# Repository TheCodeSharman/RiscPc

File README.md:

# RiscPc Repair Resources

This repository contains a collection of resources usefull for Risc PC repair.

The Risc OS 3.6.0 ROM source code is available at `external/Kernel`.

In order to view the POST messages refer to `ACORN_POST.md` that documents using a logic analsyer with a couple of resisters and a diode. This avoids needing to obtain/build a POST unit.

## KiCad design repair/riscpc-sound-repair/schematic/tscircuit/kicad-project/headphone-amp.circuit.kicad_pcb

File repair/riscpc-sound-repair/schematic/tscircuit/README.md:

# tscircuit evaluation

The same headphone amplifier as [`../headphone_amp.py`](../headphone_amp.py),
written in [tscircuit](https://tscircuit.com) instead of schemdraw — to answer
one question: **can you describe a circuit declaratively and have software
apply schematic conventions for you?**

Short answer: **yes, and it works.** Every component here is placed and every
net routed by tscircuit, from a file that contains no coordinates at all. But
the conventions it applies are weaker than a human's, and the result is
noticeably less readable than the hand-conventioned schemdraw drawing.

## Running

```bash
nix develop .#tscircuit --command make -C repair/riscpc-sound-repair/schematic/tscircuit
nix develop .#tscircuit --command make -C repair/riscpc-sound-repair/schematic/tscircuit kicad
```

`node`, `bun` (the CLI shells out to it) and `rsvg-convert` come from the
`tscircuit` devShell in `flake.nix` — kept separate from `default` so the
everyday shell stays lean. Deps come from npm, not nixpkgs.

Committed: `headphone-amp.svg`, `netlist.txt`, `package-lock.json`, and
`kicad-project/` — the extracted KiCad project.
Gitignored: `node_modules/`, the `.zip`, KiCad's `~*.lck` locks, and
`kicad-project/3dmodels/` (2.6 MB of STEP, regenerable).

**`kicad-project/` is tracked on purpose.** It starts out derived, but the
whole point of exporting to KiCad is to hand-tidy the layout there — and the
moment it is edited it stops being derived and becomes source. So it is
committed as text (`.kicad_sch`, `.kicad_pcb` and `.kicad_pro` are all
s-expressions or JSON, and diff readably), and `make kicad-project`
**overwrites it**. Check `git status` before re-running that target.

## What it got right

- **It genuinely auto-lays-out.** No `schX`/`schY` anywhere. It placed 27
  components and routed every net unaided, and the output reads as a
  schematic — op-amp triangles pointing the right way, resistors on their
  correct axis, the two channels ending up as visibly separate clusters.
- **It is a netlist, not a picture.** `netlist.txt` is a real net-by-net
  listing that can be checked against the probing notes — something schemdraw
  fundamentally cannot give, because schemdraw only draws lines.
- **KiCad export works, and it is a real file.** Verified rather than
  assumed: balanced s-expressions, format `version 20250114` (KiCad 9),
  38 symbol instances, 120 wire segments, 12 junctions, 14 global labels,
  every reference present. `make kicad-zip` gives a whole project —
  `.kicad_sch` + `.kicad_pcb` + `.kicad_pro` + STEP models.

  Caveat: symbols are tscircuit's own embedded `lib_symbols`
  (`Device:boxresistor_right`, `Custom:rail_up`), not KiCad's standard
  `Device:R`. Because `.kicad_sch` embeds its symbol definitions, it opens
  and renders standalone — but editing it against KiCad's own libraries, or
  taking it to a board with real footprints, means remapping symbols first.
- **Same mirror win as schemdraw.** `Channel` is written once and instantiated
  twice.

## What it got wrong

- **Signal flow is not left→right.** The DAC landed in the middle-right,
  feeding I/V converters to its upper-left, with `IOL` lassoed all the way
  around the left edge of the sheet.
- **Rails are not at the top, grounds not at the bottom.** `V_PLUS12` /
  `V_MINUS12` became floating net labels wherever the router happened to
  finish, and the L13/L14 supply feed ended up as a disconnected island in the
  bottom-right corner with its labels overlapping.
- **It gives up and drops a label.** Where routing a wire was awkward it emits
  a net-label stub instead — `U1D_pin2`, `U1A_pin3`, `R_s1_RIGHT_pin2` — drawn
  rotated 90°. These are the ugliest thing on the sheet and they actively hide
  the topology: the composite-amp feedback path, the single most important
  feature of this circuit, is broken up by them.
- **Op-amp supply pins are not on the symbol**, so the ±12 V feed cannot be
  drawn where it belongs.
- **`schAutoLayoutEnabled` and `schTraceAutoLabelEnabled` do nothing.** Both
  exist in `@tscircuit/props`; setting them on `<board>` produced a
  byte-identical SVG. Not wired up in this version.

## Version pinning gotcha

`@tscircuit/cli@0.1.2021` crashes on startup — `SyntaxError: Export named
'schematic_sheet_size' not found in module circuit-json` — because npm resolves
`circuit-json` to `0.0.464` while the CLI needs a newer one. Fixed with an
npm `overrides` block in `package.json` pinning `circuit-json` to `0.0.479`.
If the CLI is upgraded, try removing that override first.

## Verdict

The two tools are not competing; they answer different questions.

| | schemdraw | tscircuit |
|---|---|---|
| Layout | you apply the conventions | software applies them |
| Output quality | publication-ready | readable, not presentable |
| Netlist / ERC | none | yes |
| KiCad export | none | yes (non-idiomatic symbols) |
| Effort for this circuit | ~an hour of layout tuning | none |

For **documenting this repair**, schemdraw wins — the drawing is the
deliverable and it has to be clear. `../headphone-amp.svg` stays the one that
goes in the notes.

For **verifying the trace**, tscircuit wins, and this is not a small thing:
`netlist.txt` is machine-checkable against the probing notes in a way a drawing
never is. If op-amp #2 is ever mapped, or a repair board is ever built, this is
the file to grow.

## Superseded

This is no longer being developed. The net fragmentation above turned out to
be fatal: the plan was to export to KiCad and hand-tidy the layout there, and
you cannot tidy a schematic whose nets are broken into islands joined by
generated labels — you cannot even trace a net by eye.

[`../declarative/`](../declarative/) took over, keeping the idea (a
coordinate-free source, laid out by software, exported to KiCad) and dropping
the implementation. It owns the routing, so nets stay whole.

Kept for reference and as a cross-check: it is the same circuit described a
third time, and `netlist.txt` is still a valid thing to diff against the
probing notes.

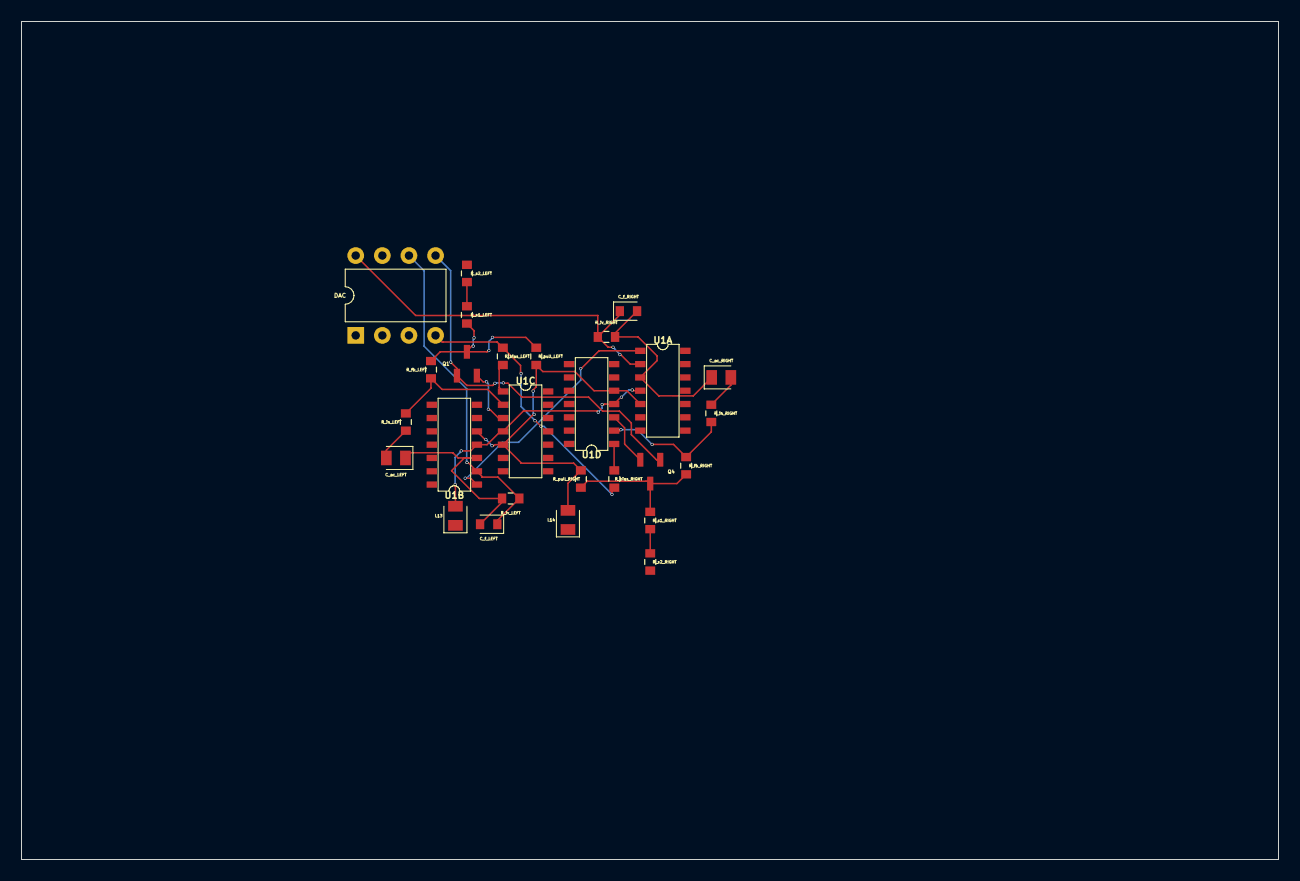
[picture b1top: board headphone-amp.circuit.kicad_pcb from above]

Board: 2 copper layers, 120.0 x 80.0 mm, 27 parts (0 on the bottom side), 21 nets.

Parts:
C_ac_LEFT: 47uF; capacitor_cap0805
C_ac_RIGHT: 47uF; capacitor_cap0805
C_f_LEFT: 100pF; capacitor_cap0603
C_f_RIGHT: 100pF; capacitor_cap0603
DAC: TDA1545A
L13, L14: 2.2µH; inductor_0805
Q1: Q1; transistor_sot23
Q4: Q4; transistor_sot23
R_bias_LEFT: 15kΩ; resistor_res0603
R_bias_RIGHT: 15kΩ; resistor_res0603
R_fb_LEFT: 47kΩ; resistor_res0603
R_fb_RIGHT: 47kΩ; resistor_res0603
R_in_LEFT: 47kΩ; resistor_res0603
R_in_RIGHT: 47kΩ; resistor_res0603
R_iv_LEFT: 2.1kΩ; resistor_res0603
R_iv_RIGHT: 2.1kΩ; resistor_res0603
R_pull_LEFT: 340Ω; resistor_res0603
R_pull_RIGHT: 340Ω; resistor_res0603
R_s1_LEFT, R_s1_RIGHT: 33Ω; resistor_res0603
R_s2_LEFT, R_s2_RIGHT: 3.3Ω; resistor_res0603
U1A: U1A; op_amp_soic14
U1B: U1B; op_amp_soic14
U1C: U1C; op_amp_soic14
U1D: U1D; op_amp_soic14

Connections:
.C_ac_LEFT > .cathode to .R_in_LEFT > .pin1: C_ac_LEFT.2, R_in_LEFT.1
.C_ac_RIGHT > .cathode to .R_in_RIGHT > .pin1: C_ac_RIGHT.2, R_in_RIGHT.1
.Q1 > .base to .U1C > .output: Q1.2, U1C.3
.Q1 > .emitter to .R_fb_LEFT > .pin1: Q1.3, R_fb_LEFT.1, R_pull_LEFT.1, R_s1_LEFT.1
.Q4 > .base to .U1D > .output: Q4.2, U1D.3
.Q4 > .emitter to .R_fb_RIGHT > .pin1: Q4.3, R_fb_RIGHT.1, R_pull_RIGHT.1, R_s1_RIGHT.1
.R_in_LEFT > .pin2 to .U1C > .inverting_input: R_fb_LEFT.2, R_in_LEFT.2, U1C.2
.R_in_RIGHT > .pin2 to .U1D > .inverting_input: R_fb_RIGHT.2, R_in_RIGHT.2, U1D.2
.R_iv_LEFT > .pin2 to .U1B > .output: C_ac_LEFT.1, C_f_LEFT.2, R_iv_LEFT.2, U1B.3
.R_iv_RIGHT > .pin2 to .U1A > .output: C_ac_RIGHT.1, C_f_RIGHT.2, R_iv_RIGHT.2, U1A.3
.R_s1_LEFT > .pin2 to .R_s2_LEFT > .pin1: R_s1_LEFT.2, R_s2_LEFT.1
.R_s1_RIGHT > .pin2 to .R_s2_RIGHT > .pin1: R_s1_RIGHT.2, R_s2_RIGHT.1
.U1C > .non_inverting_input to .R_bias_LEFT > .pin1: R_bias_LEFT.1, U1C.1
.U1D > .non_inverting_input to .R_bias_RIGHT > .pin1: R_bias_RIGHT.1, U1D.1
GND: DAC.4, R_bias_LEFT.2, R_bias_RIGHT.2
IOL: C_f_LEFT.1, DAC.6, R_iv_LEFT.1, U1B.2
IOR: C_f_RIGHT.1, DAC.8, R_iv_RIGHT.1, U1A.2
VREF: U1A.1, U1B.1
V_MINUS12: L14.2, R_pull_LEFT.2, R_pull_RIGHT.2, U1A.5, U1B.5, U1C.5, U1D.5
V_PLUS5: DAC.5, Q1.1, Q4.1
V_PLUS12: L13.2, U1A.4, U1B.4, U1C.4, U1D.4

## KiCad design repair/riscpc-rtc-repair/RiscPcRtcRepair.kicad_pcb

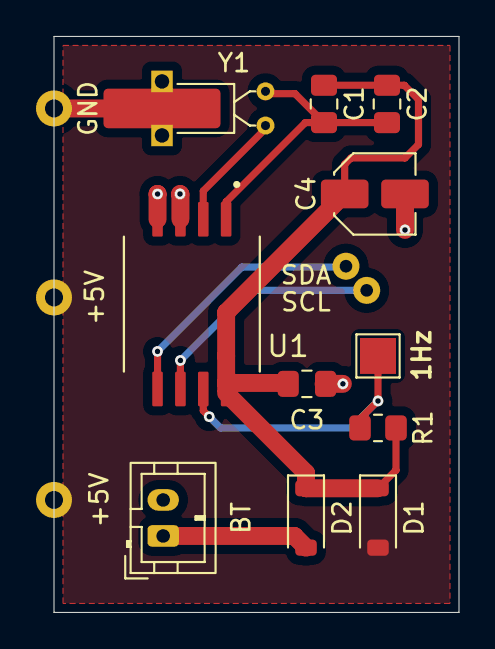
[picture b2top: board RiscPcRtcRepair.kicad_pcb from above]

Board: 2 copper layers, 22.5 x 32.0 mm, 16 parts (0 on the bottom side), 9 nets.

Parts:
+5V, +5V1: TestPoint; TestPoint_THTPad_D2.0mm_Drill1.0mm
BT: CR2032; JST_PH_B2B-PH-K_1x02_P2.00mm_Vertical
C1: 18pF; C_0805_2012Metric_Pad1.18x1.45mm_HandSolder
C2: 15pF; C_0805_2012Metric_Pad1.18x1.45mm_HandSolder
C3: C; C_0805_2012Metric_Pad1.18x1.45mm_HandSolder
C4: 4.7uF; C_Elec_4x5.4
D1, D2: BAT46W; D_SOD-123
GND: TestPoint; TestPoint_THTPad_D2.0mm_Drill1.0mm
INT1: TestPoint; TestPoint_Pad_2.0x2.0mm
R1: 4k7; R_0805_2012Metric_Pad1.20x1.40mm_HandSolder
SCL: TestPoint; TestPoint_THTPad_D1.5mm_Drill0.7mm
SDA: TestPoint; TestPoint_THTPad_D1.5mm_Drill0.7mm
U1: PCF8583T; SOIC127P1032X265-8N
Y1: Crystal_GND3; Crystal_C26-LF_D2.1mm_L6.5mm_Horizontal_1EP_style2

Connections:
+5V: +5V.1, +5V1.1, D1.2 (A)
GND: BT.2 (-), C3.1, C4.2, GND.1, U1.3 (A0), U1.4 (VSS), Y1.3
unnamed: BT.1 (+), D2.2 (A)
unnamed: C1.1, C2.1, C3.2, C4.1, D1.1 (K), D2.1 (K), R1.1, U1.8 (VDD)
unnamed: C1.2, C2.2, U1.1 (OSCI), Y1.1
unnamed: U1.2 (OSCO), Y1.2
unnamed: SCL.1, U1.6 (SCL)
unnamed: SDA.1, U1.5 (SDA)
unnamed: INT1.1, R1.2, U1.7 (~INT)

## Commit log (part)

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2025-06-09 Add interpreter for next layer up
2025-06-09 Inperpret ts_GetCommand
2025-06-09 Clean up unneeded annotation layers
2025-06-09 Begining of interpeting the LCD commands
2025-06-09 Work in progress
    I'm not sure what we're seeing but no sign of any text yet.
2025-06-09 mmake decoder compatible ith older pythons
2025-06-09 Clean up and fix acorn_post_interpreter
    Damsn Cursors code got messy quickly, this refactors the code to use aborts
    much clear way to detect sequences of commands.
2025-06-09 Refactor acorn_post
    I liked the pattern of filling a buffer and letting decoding functions
    clear the buffer if they find valid inputs.
    We can clean up the pulse detection code because this pattern gives us
    a way to implement look ahead functionality, if the decoder needs to
    look ahead but not consume a pulse it can leave it in the buffer for
    subseequence decoders to read.
2025-06-09 Print the hex value for printable characters
    When zoomed in it can be useful to see the hex encoding of the character.
2025-06-09 Clean up decoder names
    Also be more descriptive than `pd.py`
2025-06-09 Rename pd to something else
2025-06-09 Undo previous module changes
    Looks like these are mandatory for decoders so change them back.
2025-06-09 Switch back to RO_3_60
    This is the ROMS I want to referecnce for now.
2025-06-09 Update example
2025-06-09 Failing POST when RAM installed
2025-06-09 Update log.
2025-06-09 Update log with failed RAM interpretation
2025-06-09 Add details on why RAM test isn't skipped
    Also detail another ram test bug I found.
2025-06-10 POSTs from various DRAM configurations
    Looks like we might have bad contacts on the sockets.
2025-06-10 Afetr cleaning RAM we have some working RAM
2025-06-10 increas pulse duration it seems to be marginal
2025-06-10 Example of completing POST to FAIL
    We have a RAM test pass.
    VIDC fails as expected.
2025-06-12 Added somes notes and dataheet for DRAM chips
2025-06-23 updated example with VIDC bus fixed
2025-06-23 Add some more docs and tsv for vidc fail
2025-07-02 Add logic analyser during in reset
2025-07-03 Add the logic analyser data for a reset sequence
    Hoping to figure out what is going wrong - suspect signal integtrity
    of d0-7 but it doesn't look bad on the scope. So using this to try and
    correlate with instruction fetches in the early boot code.
2025-07-03 Update log
2025-07-03 Update the log with the latest repair notes
2025-07-03 Add a collection of ROMS in order to aid debugging
    Downloaded from: https://archive.org/details/RISC-OS-ROM-collection
2025-07-04 Removed my attempt a repair
    The bus integrity is not good enough with my bodge wires I could attempt
    to shield them - but I think it might be time for plan B: build a
    daughter PCB board to connect to the main baord where the pads came off.
2025-07-05 Make a start on the replacement PCB
2025-07-14 Update repair notes
2025-12-22 Completeldy PCB
2026-02-19 COmmiting updates mostly logs updates
2026-02-19 Added Ghidra dissaembly of Risc OS 3.7 ROMS
2026-02-19 Keeping git happy
2026-02-19 Updte external/Kernel
2026-02-21 Updated log and added SA110 boot trace
2026-02-26 Dissamebly of RO 3.7
2026-03-02 Update logic analyser data
    Note this is with RO 3.6 and ARM710
2026-03-02 Added a bunch of traces for freeze
2026-03-03 a bunch of traces show adress bus walk
2026-03-04 Add some logic analyser data and dissembly
2026-03-04 Add addres bus trace for current freeze
2026-03-04 commiting zip of ghidra files
2026-03-04 Remove gihdra project
    It doesn;;t work with git LOL
2026-03-04 add archive f\of ghidra analysis
2026-03-04 remove second copy of ghidra project
2026-03-04 Re-add ghidra project
    I rrealised I had the projects in two places, so re-add the correct one.
2026-03-04 add better rom checksum trace
2026-03-09 ghidra analysis update
2026-03-09 Update POST adapter hardware
2026-03-09 New trace to fix POST decoder on
2026-03-09 Fix the acorn post wire decoder
    Simplified the code by properly calculating the interbit interval from
    the sample rate.
2026-03-10 Improve comment
2026-03-10 Add RO 3.7 ROMS imaged from my machine
    This should be identical to the official ones
2026-03-10 Use correct datasheet for EPROMs
2026-04-12 Some random updates
    - Fix ACORN POST notes becasue we don't need that resister anymore.
    - The ROMS are acutally 27C160 not 27C800
    - add some POST failures in examples
    - update stray ghidra databse file.
2026-04-12 random updates
2026-04-12 Rename RiscPcPcbRepair to RiscPcVideoBusRepair
    Also make some revisions to the board to fix the bodges I need to make:
    - add castelled holes to the 5V plane
    - move a trace to the back in order to route 5V so they are connected
2026-04-13 Updte RTC schematic and notes
2026-04-14 Finished RTC repair board
2026-05-03 Built RTC board
2026-05-04 Manufactured board
2026-05-04 Revision 2 to the RTL board
    Fixes all the issues we found:
    - wrong footprint
    - missing decoupling cap
    - new ground castellation
    - switched to 0805 for easy soldering
2026-05-04 Fix warnings and add gerbers
2026-05-23 change diode to TS4148
    Higher voltage drop but that doesn't matter but crucially Schottky
    diodes are not suitable for this application as they have reverse current
    leakage which whilst probably fine isn't ideal in this application.
2026-05-23 Add PCF8583 bench-test scripts for RTC repair
    Two Bus Pirate scripts for verifying a PCF8583 RTC before/after soldering:
    i2c_test.py runs the 7-bit address scan and dumps the time/date registers,
    ram_test.py exercises the full 240-byte CMOS RAM with two patterns and
    restores the original contents.
2026-05-24 Update notes and add bench test scripts
2026-06-14 add VRAM datasheet
2026-06-17 update kicad and gihedra files
2026-06-28 Tidy up directory structure and move files to appropriate locations.
